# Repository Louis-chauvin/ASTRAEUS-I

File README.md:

<div align="center">

# ★ ASTRAEUS

**An open-source rocket flight computer, and the rocket built to fly it.**

Designed and built by Louis Chauvin, with Stan Chauvin · Dubai · 2026

`ESP32-S3` · `±200 g sensing` · `2 pyro channels` · `4 servo channels` · `microSD logging` · `fits a 35 mm tube`

</div>

---

## What is ASTRAEUS?

ASTRAEUS is a student project to design, build and fly a complete amateur rocket system from scratch:

1. **ASTRAEUS Rev A**: a custom flight computer that records every flight at high rate, finds apogee, fires the parachute, and is ready for active stabilisation (thrust-vector control).
2. **ASTRAEUS I**: a 1-metre, 54 mm rocket designed around the board, simulated and checked in OpenRocket.
3. **KNSB-38**: our own 38 mm sugar-propellant solid motor, designed in openMotor, with a static test stand.

Everything here (schematics, PCB layout, firmware, rocket design, cutting files) is open, so that YOU can learn from it, reuse it, or build your own.

> **Status (November 2026):** Rev A boards are going to be manufactured and assembled by JLCPCB (If we get funding). The breadboard prototype works and the bring-up firmware is written. ASTRAEUS I is fully designed, and the motor is in testing. No flight yet; this README will be updated with real flight data.

---

## Contents

- [The flight computer](#the-flight-computer-astraeus-rev-a)
- [The rocket](#the-rocket-astraeus-i)
- [The motor](#the-motor-knsb-38)
- [Repository layout](#repository-layout)
- [Build it yourself](#build-it-yourself)
- [Safety](#safety)
- [Roadmap](#roadmap)
- [How it was made](#how-it-was-made)
- [License](#license)

---

## The flight computer: ASTRAEUS Rev A

The goal was a board that is **small, rugged and professional**; every chip soldered directly to one PCB, with no stacked modules or breakout boards to shake loose. The white-and-gold look is inspired by Joe Barnard's (BPS.space) AVA and Signal R2 board which we found quite cool.

### Specifications

| | |
|---|---|
| **Size** | 30 × 108 mm, 1.6 mm, 4 layers. Fits a 35 mm inner-diameter tube |
| **Mass** | ≈ 21 g assembled |
| **Processor** | ESP32-S3 (dual-core 240 MHz, Wi-Fi + Bluetooth, 8 MB flash), native USB-C |
| **Motion sensor** | ST LSM6DSO32: ±32 g accelerometer, ±2000 °/s gyroscope |
| **High-g sensor** | Analog Devices ADXL375: ±200 g accelerometer (motor spikes, ejection shock) |
| **Barometer** | Bosch BMP388 (≈ ±0.5 m relative altitude) |
| **Logging** | microSD on its own SPI bus, so writing never stalls the sensor reads |
| **Pyro** | 2 low-side MOSFET channels, hardware ARM switch, continuity sensing, red ARMED LED |
| **Servos** | 4 channels on a dedicated 5 V / 2 A supply, for thrust-vector control |
| **Status** | Passive buzzer (2.7 kHz), white status LED, green power LED, BOOT and RESET buttons |
| **Power** | 2S LiPo (6.0–8.4 V), reverse-battery protection, separate 3.3 V logic and 5 V servo converters. USB-C alone powers the logic for bench work |

<br clear="right">

### Design decisions

- **Three separate power paths.** Logic (3.3 V), servos (5 V) and pyro each get their own supply, so a stalled servo or a firing e-match can't brown-out the processor mid-flight.
- **Pyro channels that can't fire by accident.** Gate pull-down resistors hold the MOSFETs off during boot and reset. The ARM switch physically disconnects the pyro supply, and the ARMED LED is driven by hardware, not software.
- **Two accelerometers.** The LSM6DSO32 is precise up to ±32 g; the ADXL375 takes over when motor ignition or ejection shocks go past that.
- **4-layer stack-up.** A solid ground plane sits under every sensor for clean measurements. The antenna end is kept free of copper on all four layers so Wi-Fi works through the airframe.
- **Built for flight loads.** Six M2 mounting holes keep the first bending mode near 750 Hz (estimate). Thrust acts in the plane of the board, where it is stiffest. The microSD slot faces sideways, so acceleration along the rocket can't push the card's latch.
- **Status you can hear.** On the launch pad the board is sealed inside the rocket, so it reports by buzzer: one long beep means all checks passed; numbered beeps identify a fault; one beep per channel confirms each connected igniter.

### ESP32-S3 pin map

| GPIO | Function | | GPIO | Function |
|---|---|---|---|---|
| 12 · 11 · 13 | Sensor SPI: SCK · MOSI · MISO | | 40 · 41 | Pyro 1 · 2 gate |
| 10 · 8 | IMU chip select · interrupt | | 1 · 2 | Pyro 1 · 2 continuity sense |
| 14 · 9 | High-g chip select · interrupt | | 6 · 7 · 15 · 16 | Servo 1 – 4 |
| 18 · 17 | Barometer chip select · interrupt | | 21 | Buzzer |
| 36 · 35 · 37 · 38 | microSD SCK · MOSI · MISO · CS | | 42 | Status LED |
| 19 · 20 | USB D− · D+ | | 4 · 5 | Battery · pyro-rail voltage sense |
| 0 | BOOT button (also a user button) | | 47 · 48 · 43 · 44 | Spare GPIO and UART on test pads |

The same map is in [`firmware/selftest/astraeus_pins.h`](firmware/selftest/astraeus_pins.h).

### Layout

*Left to right: top (parts and short signals over a ground fill), inner 1 (solid ground plane), inner 2 (long signal runs with a 3.3 V fill), bottom (remaining signals, solder pads, ground fill).*

Board facts:
- 0.15 mm minimum trace and clearance, 0.3 mm vias.
- Every net routed, with 0 design-rule errors.
- The battery, power switch and arm switch connect to flat solder pads on the underside, because side connectors wouldn't clear the tube wall.

---

## The rocket; ASTRAEUS I

A 54 mm (LOC Precision 2.14") rocket for a 38 mm motor. It flies ASTRAEUS in an electronics bay at its middle, with a single parachute deployed electronically at apogee. Its parts come from standard suppliers (LOC Precision, Fruity Chutes, Aero Pack). The fins and thrust rings are laser-cut from birch plywood, and the electronics sled is 3D-printed.

### Predicted performance (OpenRocket)

| | Own KNSB motor (estimated curve) | Cesaroni 338I180 (first flight) |
|---|---|---|
| Apogee | ≈ 1,040 m | ≈ 1,260 m |
| Top speed | 186 m/s (Mach 0.53) | 230 m/s |
| Peak acceleration | 20 g | 16 g |
| Stability | 2.65 → 3.2 calibers (≥ 2.0 through ascent) | 3.3 → 4.1 calibers |
| Normal-force coefficient CNα | 18 – 19 | 18 – 19 |
| Rail exit speed (2 m rail) | 25 m/s | 22 m/s |
| Descent rate | 5.0 m/s | 4.5 m/s |
| Liftoff mass | 1,648 g | 1,322 g |

### Airframe

| | |
|---|---|
| **Length / diameter** | 1,027 mm / 57.4 mm |
| **Nose cone** | LOC PNC-2.14 ogive, with 50 g of nose weight for stability margin in crosswinds |
| **Avionics bay** | LOC EB-2.14 coupler with a gold switch band. Holds ASTRAEUS, a 2S 450 mAh LiPo, the power and arm switches, and the ejection charge wells |
| **Fins** | 4 × clipped delta, 3/16" (4.8 mm) birch aircraft plywood, through-the-wall. Flutter speed ≈ 300 m/s, about 1.5× the rocket's top speed |
| **Motor mount** | 38 mm × 14", three centering rings, Aero Pack screw-on retainer |
| **Recovery** | 36" Fruity Chutes elliptical, 15 ft Kevlar shock cord, Nomex blanket. Primary charge at apogee, back-up 1.5 s later |

<p align="center">
<br>
<br>
<em>OpenRocket's own 3D and cut-away views: e-bay, packed parachute, shock cord, motor and nose weight, all to scale.</em>
</p>

---

## The motor; KNSB-38

A 38 mm solid motor using KNSB (potassium nitrate and sorbitol "sugar" propellant) in four BATES grains. It sits on the H/I-class boundary, at roughly 300–330 N·s total impulse over about 1.2 s. The aluminium casing and steel nozzle were designed in CAD, and the internal ballistics were simulated in openMotor. A vertical static test stand with a load cell is used to measure the real thrust curve before any flight.

> The thrust curve in [`rocket/LChauvin_KNSB38.eng`](rocket/LChauvin_KNSB38.eng) is an **estimate**. It will be replaced with the measured static-test curve.

---

## Repository layout

```
astraeus/
├── hardware/
│   ├── kicad/            KiCad 7 project (board, footprint library, layout scripts)
│   └── fabrication/      Gerbers, drill, BOM and placement files for JLCPCB, 1:1 print
├── firmware/
│   ├── selftest/         Bring-up test for Rev A + astraeus_pins.h
│   └── breadboard-prototype/   v1.1 logger used on the breadboard prototype
├── rocket/               OpenRocket design, motor curve, laser-cut fins (DXF), decals
└── images/
```

---

## Build it yourself

### 1. Order the board

The files in [`hardware/fabrication`](hardware/fabrication) are ready for JLCPCB with factory assembly:

| Setting | Value |
|---|---|
| Layers | 4, 1.6 mm, FR-4 |
| Colour | White solder mask, black silkscreen |
| Surface | ENIG (flat gold pads for the tiny LGA sensors) |
| Copper | 1 oz outer, 0.5 oz inner |
| Vias | Tented or plugged, 0.3 mm minimum hole |
| Assembly | Top side, Standard PCBA. Upload `ASTRAEUS_BOM_JLCPCB.csv` and `ASTRAEUS_CPL_JLCPCB.csv` |

In the 3D placement preview, check that each chip's pin-1 dot matches the board marking. You solder the 3 × 4 right-angle servo header and the wires yourself.

### 2. First power-up

1. Plug in USB-C, with no battery. The green PWR LED should light and a serial port should appear.
2. In the Arduino IDE, choose *ESP32S3 Dev Module*, *USB CDC On Boot: Enabled*, *Flash 8 MB*. Upload [`astraeus_selftest.ino`](firmware/selftest/astraeus_selftest.ino).
3. Listen: a rising chirp, then **one long beep** means every chip answered. Short beeps identify a fault: 1 IMU, 2 high-g, 3 barometer, 4 SD card.
4. Serial commands:
   - `r` reads the sensors
   - `v` reads the battery voltage
   - `s` sweeps the servos
   - `FIRE1` / `FIRE2` pulse a pyro channel, **bench test with an LED + 1 kΩ resistor only**

### 3. Build the rocket

Open [`rocket/ASTRAEUS_I.ork`](rocket/ASTRAEUS_I.ork) in OpenRocket 24.12 or later. First copy the `.eng` file into OpenRocket's ThrustCurves folder, so the custom motor loads. Then:
- Laser-cut the fins and thrust rings from [the DXF](rocket/ASTRAEUS_I_fins_laser_4.8mm_ply.dxf) in 4.8 mm birch plywood.
- Print the decals at 100 % from [the decal sheet](rocket/ASTRAEUS_I_decal_sheet_1to1.pdf).

---

## Safety

- **Arm only on the launch pad.** Never connect an igniter to an armed board indoors or on a bench.
- **Ground-test the ejection charges** with the rocket fully packed before the first flight.
- **Static-test home-made motors** before flying them, and fly only with a club or national rocketry body, following its rules. Black powder, e-matches and rocket motors are regulated in many countries, including the UAE.
- LiPo batteries: charge with a proper balance charger, never unattended.

---

## Roadmap

- [x] Breadboard prototype: ESP32 + barometer + IMU + microSD logging
- [x] ASTRAEUS Rev A designed, ordered, factory-assembled
- [x] ASTRAEUS I rocket designed and simulated
- [ ] Rev A bring-up and bench tests
- [ ] Flight firmware: all three sensors, high-rate logging, flight state machine, buzzer status
- [ ] Motor static fires and measured thrust curve
- [ ] First flight (commercial motor), then flights on our own KNSB motor
- [ ] Electronic deployment validated in flight
- [ ] Attitude estimation and thrust-vector control

---

## License

- **Hardware** (KiCad files, fabrication files, rocket design): [CERN-OHL-S v2](https://ohwr.org/cern_ohl_s_v2.txt)
- **Firmware:** [MIT](https://opensource.org/license/mit)

You're welcome to build, modify and share ASTRAEUS. Please credit the project and share your improvements.

---

<div align="center">

★ **ASTRAEUS** · L. Chauvin · 2026

*Named after Astraeus, the Titan of the stars and the dusk winds.*

</div>

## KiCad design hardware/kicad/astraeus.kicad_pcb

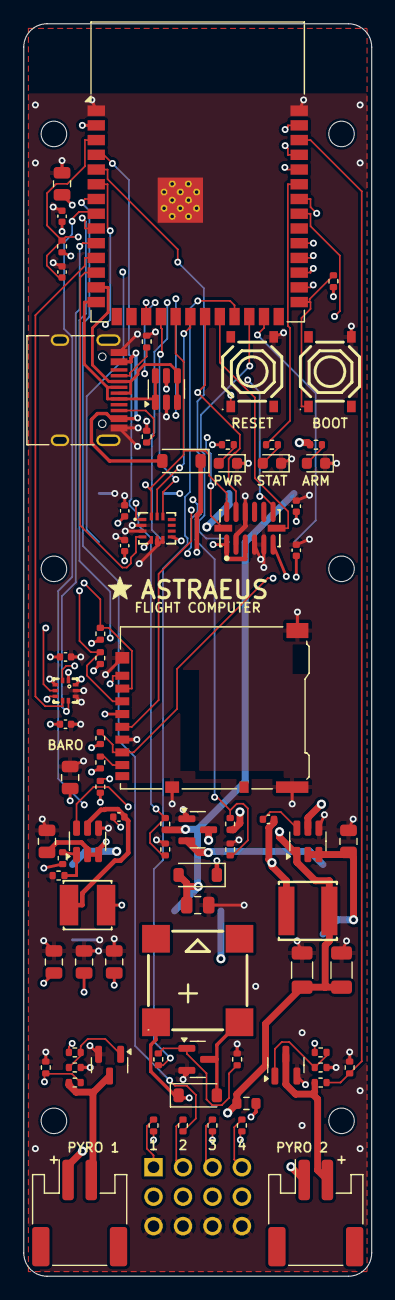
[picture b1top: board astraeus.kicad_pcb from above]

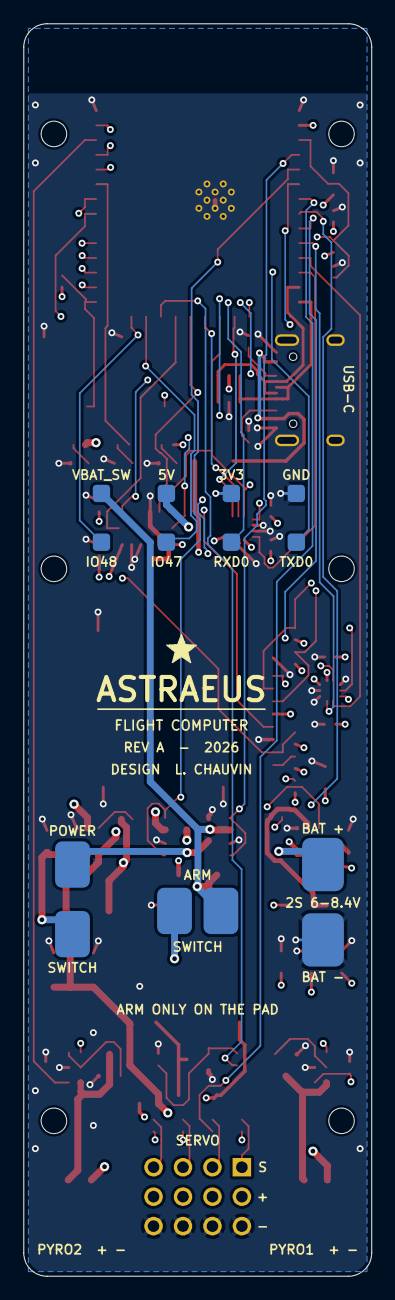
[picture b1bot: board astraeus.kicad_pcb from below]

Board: 4 copper layers, 30.0 x 108.0 mm, 100 parts (14 on the bottom side), 65 nets.

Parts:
BZ1: MLT-8530; BUZ-SMD_4P-L8.5-W8.5-P8.50-BR
C1, C16, C30, C40, C44: 10u; C_0805_2012Metric
C2, C10, C11, C12, C14, C15, C31, C41: 100nF; C_0402_1005Metric
C3, C13: 1uF; C_0402_1005Metric
C32, C33, C34: 22uF; C_0805_2012Metric
C42, C43: 47uF; C_1206_3216Metric
D1, D2: B5819W; D_SOD-123
D3: 1N4148W; D_SOD-123
D10: PWR green; LED_0603_1608Metric
D11: STATUS white; LED_0603_1608Metric
D12: ARMED red; LED_0603_1608Metric
H1, H2, H3, H4, H5, H6: MountingHole_2.2mm_M2
J1: TYPE-C-31-M-12; USB_C_Receptacle_HRO_TYPE-C-31-M-12
J2: DM3AT-SF-PEJM5; microSD_HC_Hirose_DM3AT-SF-PEJM5
J3: PYRO1 JST-PH; JST_PH_S2B-PH-SM4-TB_1x02-1MP_P2.00mm_Horizontal
J4: PYRO2 JST-PH; JST_PH_S2B-PH-SM4-TB_1x02-1MP_P2.00mm_Horizontal
J5: SERVO 3x4 right-angle 2.54; ServoRail_3x4_P2.54mm_Horizontal
L1: 4.7uH SWPA4020S4R7MT; IND-SMD_L4.0-W4.0
L2: 6.8uH SWPA5040S6R8MT; IND-SMD_L5.0-W5.0_SWPA5040S
Q1, Q2, Q3: AO3400A; SOT-23
Q5: AO3401A (reverse-battery); SOT-23
R1, R2, R20, R21, R22, R23, R24: 10k; R_0402_1005Metric
R3, R4: 5k1; R_0402_1005Metric
R10, R11, R41: 1k; R_0402_1005Metric
R12: 2k2; R_0402_1005Metric
R30, R32, R42, R51, R52, R55, R56, R71: 100k; R_0402_1005Metric
R31, R33: 22k; R_0402_1005Metric
R40: 10R; R_0603_1608Metric
R50, R54, R60, R61, R62, R63: 100R; R_0402_1005Metric
R53, R57, R70: 33k; R_0402_1005Metric
SW1: BOOT TS-1187A; SW-SMD_4P-L5.1-W5.1-P3.70-LS6.5-TL_H1.5
SW2: RESET TS-1187A; SW-SMD_4P-L5.1-W5.1-P3.70-LS6.5-TL_H1.5
TP1: BAT+; SolderPad_3.6x4.6mm
TP2: BAT-; SolderPad_3.6x4.6mm
TP3, TP4: SW; SolderPad_3.0x4.0mm
TP5, TP6: ARM; SolderPad_3.0x4.0mm
TP10: GND; SolderPad_1.6x1.6mm
TP11: +3V3; SolderPad_1.6x1.6mm
TP12: +5V; SolderPad_1.6x1.6mm
TP13: VBAT_SW; SolderPad_1.6x1.6mm
TP14: TXD0; SolderPad_1.6x1.6mm
TP15: RXD0; SolderPad_1.6x1.6mm
TP16: IO47; SolderPad_1.6x1.6mm
TP17: IO48; SolderPad_1.6x1.6mm
U1: ESP32-S3-WROOM-1-N8; ESP32-S3-WROOM-1
U2: LSM6DSO32TR; LGA-14_L3.0-W2.5-P0.50-TL
U3: ADXL375BCCZ-RL7; LGA-14_L5.0-W3.0-P0.80-BL
U4: BMP388; SENSORM-SMD_BMP388
U5: AP63200WU-7; TSOT-23-6
U6: AP63205WU-7; TSOT-23-6
U7: USBLC6-2SC6; SOT-23-6

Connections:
+3V3: C1.1, C2.1, C10.1, C11.1, C12.1, C13.1, C14.1, C15.1, C16.1, C32.1, C33.1, C34.1, J2.4, L1.2, R1.1, R2.1, R10.1, R20.1, R21.1, R22.1, R23.1, R24.1, R71.1, TP11.1, U1.2, U2.5, U2.8, U3.1, U3.3, U3.6, U4.1, U4.10
+5V: C42.1, C43.1, J5.P1, J5.P2, J5.P3, J5.P4, L2.2, R40.1, TP12.1, U6.1
BOOT: R2.2, SW1.1, U1.27
BST3: C31.1, U5.6
BST5: C41.1, U6.6
BUZ: R41.1, U1.23
BUZ_D: BZ1.2, D3.2, Q3.3
BUZ_G: Q3.1, R41.2, R42.1
BZ_P: BZ1.1, D3.1, R40.2
CC1: J1.A5, R3.1
CC2: J1.B5, R4.1
CS_BARO: U1.11, U4.6
CS_HG: U1.22, U3.7
CS_IMU: U1.18, U2.12
EN: C3.1, R1.2, SW2.1, U1.3
FB3: R70.2, R71.2, U5.1
GND: C1.2, C2.2, C3.2, C10.2, C11.2, C12.2, C13.2, C14.2, C15.2, C16.2, C30.2, C32.2, C33.2, C34.2, C40.2, C42.2, C43.2, C44.2, D10.1, D11.1, D12.1, J1.A1, J1.A12, J1.B1, J1.B12, J1.S1, J2.6, J2.11, J5.G1, J5.G2, J5.G3, J5.G4, Q1.2, Q2.2, Q3.2, Q5.1, R3.2, R4.2, R31.2, R33.2, R42.2, R51.2, R53.2, R55.2, R57.2, R70.1, SW1.4, SW2.4, TP2.1, TP10.1, U1.1, U1.40, U1.41, U2.2, U2.3, U2.6, U2.7, U3.2, U3.4, U3.5, U3.11, U4.3, U4.8, U4.9, U5.4, U6.4, U7.2
INT_BARO: U1.10, U4.7
INT_HG: U1.17, U3.8
INT_IMU: U1.12, U2.4
IO47: TP16.1, U1.24
IO48: TP17.1, U1.25
LED_AR: D12.2, R12.2
LED_PWR: D10.2, R10.2
LED_ST: D11.2, R11.2
LED_STAT: R11.1, U1.35
PY1_D: J3.2, Q1.3, R52.1
PY1_G: Q1.1, R50.2, R51.1
PY1_GATE: R50.1, U1.33
PY1_SENSE: R52.2, R53.1, U1.39
PY2_D: J4.2, Q2.3, R56.1
PY2_G: Q2.1, R54.2, R55.1
PY2_GATE: R54.1, U1.34
PY2_SENSE: R56.2, R57.1, U1.38
RXD0: TP15.1, U1.36
SD_CS: J2.2, R20.2, U1.31
SD_D1: J2.8, R23.2
SD_D2: J2.1, R24.2
SD_MISO: J2.7, R22.2, U1.30
SD_MOSI: J2.3, R21.2, U1.28
SD_SCK: J2.5, U1.29
SERVO1: R60.1, U1.6
SERVO2: R61.1, U1.7
SERVO3: R62.1, U1.8
SERVO4: R63.1, U1.9
SPI_MISO: U1.21, U2.1, U3.12, U4.5
SPI_MOSI: U1.19, U2.14, U3.13, U4.4
SPI_SCK: U1.20, U2.13, U3.14, U4.2
SRV1: J5.S1, R60.2
SRV2: J5.S2, R61.2
SRV3: J5.S3, R62.2
SRV4: J5.S4, R63.2
SW3: C31.2, L1.1, U5.5
SW5: C41.2, L2.1, U6.5
TXD0: TP14.1, U1.37
USB_DN: J1.A7, J1.B7, U1.13, U7.3, U7.4
USB_DP: J1.A6, J1.B6, U1.14, U7.1, U7.6
VBAT: Q5.2, TP3.1
VBAT_IN: Q5.3, TP1.1
VBAT_SENSE: R30.2, R31.1, U1.4
VBAT_SW: C40.1, C44.1, D1.2, R30.1, TP4.1, TP5.1, TP13.1, U6.2, U6.3
VBUS: D2.2, J1.A4, J1.A9, J1.B4, J1.B9, U7.5
VLOGIC: C30.1, D1.1, D2.1, U5.2, U5.3
VPYRO: J3.1, J4.1, R12.1, R32.1, TP6.1
VPYRO_SENSE: R32.2, R33.1, U1.5

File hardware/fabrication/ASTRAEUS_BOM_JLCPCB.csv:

Comment,Designator,Footprint,LCSC Part #
ESP32-S3-WROOM-1-N8,U1,ESP32-S3-WROOM-1,C2913198
10u,"C1,C16,C30,C40,C44",C_0805_2012Metric,C15850
100nF,"C2,C10,C11,C12,C14,C15,C31,C41",C_0402_1005Metric,C1525
10k,"R1,R2,R20,R21,R22,R23,R24",R_0402_1005Metric,C25744
1uF,"C3,C13",C_0402_1005Metric,C52923
TYPE-C-31-M-12,J1,USB_C_Receptacle_HRO_TYPE-C-31-M-12,C165948
USBLC6-2SC6,U7,SOT-23-6,C2827654
5k1,"R3,R4",R_0402_1005Metric,C25905
B5819W,"D1,D2",D_SOD-123,C8598
TS-1187A,"SW1,SW2",SW-SMD_4P-L5.1-W5.1-P3.70-LS6.5-TL_H1.5,C318884
PWR green,D10,LED_0603_1608Metric,C12624
1k,"R10,R11,R41",R_0402_1005Metric,C11702
STATUS white,D11,LED_0603_1608Metric,C2290
ARMED red,D12,LED_0603_1608Metric,C2286
2k2,R12,R_0402_1005Metric,C25879
LSM6DSO32TR,U2,LGA-14_L3.0-W2.5-P0.50-TL,C1864162
ADXL375BCCZ-RL7,U3,LGA-14_L5.0-W3.0-P0.80-BL,C481898
BMP388,U4,SENSORM-SMD_BMP388,C779278
DM3AT-SF-PEJM5,J2,microSD_HC_Hirose_DM3AT-SF-PEJM5,C114218
AO3401A (reverse-battery),Q5,SOT-23,C15127
100k,"R30,R32,R42,R51,R52,R55,R56,R71",R_0402_1005Metric,C25741
22k,"R31,R33",R_0402_1005Metric,C25768
AP63200WU-7,U5,TSOT-23-6,C2071868
4.7uH SWPA4020S4R7MT,L1,IND-SMD_L4.0-W4.0,C48427
22uF,"C32,C33,C34",C_0805_2012Metric,C45783
AP63205WU-7,U6,TSOT-23-6,C2071056
6.8uH SWPA5040S6R8MT,L2,IND-SMD_L5.0-W5.0_SWPA5040S,C36411
47uF,"C42,C43",C_1206_3216Metric,C96123
MLT-8530,BZ1,BUZ-SMD_4P-L8.5-W8.5-P8.50-BR,C94599
AO3400A,"Q1,Q2,Q3",SOT-23,C20917
1N4148W,D3,D_SOD-123,C81598
10R,R40,R_0603_1608Metric,C22859
JST-PH,"J3,J4",JST_PH_S2B-PH-SM4-TB_1x02-1MP_P2.00mm_Horizontal,C295747
100R,"R50,R54,R60,R61,R62,R63",R_0402_1005Metric,C25076
33k,"R53,R57,R70",R_0402_1005Metric,C25779

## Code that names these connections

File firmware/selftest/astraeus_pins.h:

// ASTRAEUS Rev A - flight computer pin map (ESP32-S3-WROOM-1-N8)
// Matches the routed KiCad board. Include this in every ASTRAEUS sketch.
#pragma once

// ---- sensor SPI bus (FSPI): LSM6DSO32 IMU, ADXL375 high-g, BMP388 baro
#define PIN_SPI_SCK     12
#define PIN_SPI_MOSI    11
#define PIN_SPI_MISO    13
#define PIN_CS_IMU      10   // LSM6DSO32  (±32 g, ±2000 dps)
#define PIN_CS_HG       14   // ADXL375    (±200 g)
#define PIN_CS_BARO     18   // BMP388
#define PIN_INT_IMU      8   // LSM6DSO32 INT1
#define PIN_INT_HG       9   // ADXL375 INT1
#define PIN_INT_BARO    17   // BMP388 INT

// ---- microSD, own SPI bus (HSPI) so logging never blocks sensor reads
#define PIN_SD_SCK      36
#define PIN_SD_MOSI     35
#define PIN_SD_MISO     37
#define PIN_SD_CS       38

// ---- pyro channels: low-side AO3400A, 100k gate pull-down (off at boot)
#define PIN_PY1_GATE    40
#define PIN_PY2_GATE    41
#define PIN_PY1_SENSE    1   // ADC: drain voltage x 33/133  -> continuity
#define PIN_PY2_SENSE    2

// ---- servos (TVC): 5 V rail from AP63205, 100R series on each signal
#define PIN_SERVO1       6
#define PIN_SERVO2       7
#define PIN_SERVO3      15
#define PIN_SERVO4      16

// ---- status
#define PIN_BUZZER      21   // passive MLT-8530 via AO3400A, drive 2.7 kHz
#define PIN_LED_STAT    42   // white status LED (high = on)
#define PIN_BOOT         0   // BOOT button, active low (also usable as user button)

// ---- power monitoring (ADC, 11 dB attenuation)
#define PIN_VBAT_SENSE   4   // battery after power switch, x 22/122
#define PIN_ARM_SENSE    5   // pyro rail after ARM switch, x 22/122
#define VBAT_DIVIDER     (122.0f / 22.0f)
#define PYRO_DIVIDER     (133.0f / 33.0f)

// ---- spare GPIO on bottom test pads
#define PIN_SPARE1      47
#define PIN_SPARE2      48
// UART0 TX/RX are also on bottom test pads (GPIO43 / GPIO44)

// ---- buzzer
#define BUZZER_HZ       2700
